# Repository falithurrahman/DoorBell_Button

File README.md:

### Description
In this repository, i made a doorbell using ESP8266-01 as a controller. This doorbell will play local mp3 file as notification sound through 3.5mm audio jack in my laptop, since i install home assistant server on docker in Ubuntu laptop. The audio jack in my laptop is connected to external speaker that will boost notification sound volume. I will cover up the details of this project in 2 parts. First is setting up doorbell hardware. Second is configuring home assistant server.

### First part, Doorbell Hardware

#### Tools and Equipments
Here is the parts we need to make physical doorbell button.
* ESP8266-01 Module
* Push Button
* BD140 Transistor
* 2x 18650 Li-Ion Battery
* 2x 5mm LED Indicator

#### Wiring Diagram
This section will cover wiring diagram from doorbell button. The detailed schematic and board file can be downloaded in the controller board folder. <br>

I used 2x 18650 Li-Ion battery to power this circuit. Those batteries will have parallel connection to increase the capacity (mAh). Higher capacity will make this battery more durable. I have tried this configuration, and the battery i use can last 4-5 days. So i have to replace the battery once every 4-5 days for charging.

#### Code
I use ESPHome firmware running on ESP8266-01 device. Since i use ESPHome, the code will be in yaml file. You can download the code inside Code folder with ESP01_BellControl.yaml filename. Pushbutton and indicator LED are attached to GPI02 and GPIO0 respectively. Button debounce filter is added to binary sensor in order to minimize misreading which is caused by debounce.
````yaml
switch:
  - platform: gpio
    id: indikator
    inverted: true
    name: LED Indikator
    pin: GPIO0

binary_sensor:
  - platform: gpio
    id: button
    name: Doorbell Button
    pin:
      number: GPIO2
      mode: INPUT_PULLUP
      inverted: true
    filters:
      - delayed_on: 25ms
      - delayed_off: 25ms
````

### Second Part, Home Assistant Configuration

#### Software Requirement
I am intended to make customized mp3 file played as notification sound through 3.5mm audio jack. This file is stored in local hard drive inside home assistant server. An add-ons is need to be installed to fulfill this purpose. To install the add-ons, follow these steps.
* In your home assisstant, go to supervisor -> Add-ons Store.
* Under repositories part, where we configure which add-on repositories to fetch data from, copy-paste this link. Then click 'Add'. It might take a bit, be patient. <br>
https://github.com/bestlibre/hassio-addons
* When the add-ons successfully installed, start the service.
* Add these line to your configuration.yaml file 
````yaml
# Mopidy addon for hass.io
media_player:
  platform: mpd
  host: YOUR.HOST.IP
````
* Restart home assistant server. Now we have Mopidy add-ons running in home assistant server.

After installing the add-ons, we need to configure it. As we can see at mopidy add-ons page, there are several variables that we can configure. Since our purpose is to play local mp3 file as notification sound, we need to enable local file scan and set the directory where the mp3 is stored. It can be done by writing these line
````yaml
local_scan: true
options:
  - name: local/media_dir
    value: /share/mopidy/media
````
In the example above, i place my mp3 file inside /share/mopidy/media. Then, restart home assistant server.

Next step, we will play the audio file stored in local drive through home assistant. To play the audio, follow the steps below.
* Go to Mopidy add-ons store page, and open web user interface. 
* We will see there are three options: image, iris, moped.Click on iris.
   
* At iris homepage, go to browse -> local media -> tracks
  <p align="center">
   <br>
   <br>
   <br>
  </p>
Or in short, you can access the link below <br>
http://"home_assistant_server_IP":6680/iris/library/browse/local%3Adirectory%3Ftype%3Dtrack <br>
Replace home_assistant_server_IP with the IP of home assistant without "" mark. <br>
* Find audio file we need, click on the three dots (...) and click on "Copy URI". Now we have the internal ID of this file in our clipboard. <br>
  <p align="center">
   <br>
   <br>
  </p>
* Go to developer tools -> service tab. Choose 'media_player.play_media' for service and 'media_player.mpd' for entity. For service data, fill it with line below
    ````yaml
    {
    "entity_id": "media_player.mpd",
    "media_content_type": "music",
    "media_content_id": "..."
    }
    ````
    Replace the media_content_id value with the URI file we copy. <br>
    <p align="center">
     <br>
    </p>
* Click "Call Service". The file should now be played via the 3.5mm headphone jack. Now we can use it in any automation.

#### Adding Automation
Now we reached the step when we finished configuring both hardware and software. The last step is to combine both of them by creating automation. I attach my automation.yaml file inside code folder. There are several things that i'd like to highlight. First is volume setting for our mp3 audio notification. We can adjust the volume by calling service called `media_player.volume_set`. The volume that we can set ranged from 0 to 1. I use 0.5 in my automation.
````yaml
  action:
  - data:
      entity_id: media_player.mpd
      volume_level: 0.5
    entity_id: media_player.mpd
    service: media_player.volume_set
````
Second is notification feature within home assistant apps. If we installed home assistant in our android or iOS phone, we can send a push notification everytime the automation happens. We do it by call service named `notify`. If we have more than one device and we want to send the notification at once, we have to modify `configuration.yaml` file. We add this line. `service:` is the name of our device. We can add more than one device.
````yaml
notify:
  - name: ALL_DEVICES
    platform: group
    services:
      - service: mobile_app_mi_9
      - service: mobile_app_asus_z010d
      - service: mobile_app_asus_z00ed
      - service: mobile_app_asus_t00f
````
Within the `automation.yaml` file, we call `notify.all_devices` service since the group name of our device is `ALL_DEVICES` in the `configuration.yaml file`.
````yaml
  action:
  - data:
      message: Ada Tamu!
    service: notify.all_devices
````

#### References
* TTS using built in RPi3 analogue audio output with Hassio <br>
https://community.home-assistant.io/t/tts-using-built-in-rpi3-analogue-audio-output-with-hassio/32475
*

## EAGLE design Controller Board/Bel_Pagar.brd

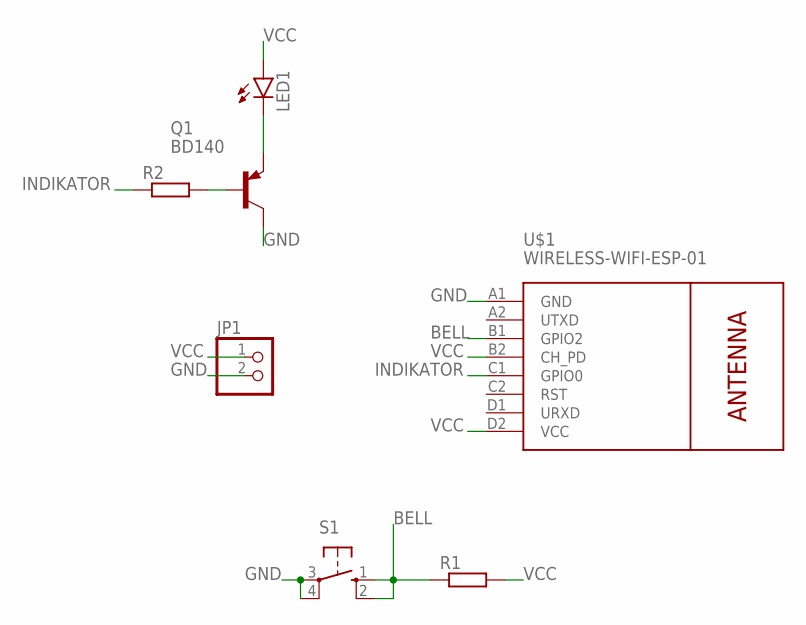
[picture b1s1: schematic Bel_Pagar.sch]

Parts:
JP1: PINHD-1X2; 1X02
LED1: LED5MM
Q1: BD140; TO126
R1, R2: R-EU_0207/10; 0207/10
S1: 10-XX; B3F-10XX
U$1: WIRELESS-WIFI-ESP-01

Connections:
BELL: R1.1, S1.1 (S), S1.2 (S1), U$1.B1 (GPIO2)
GND: JP1.2, Q1.2 (C), S1.3, S1.4 (P1), U$1.A1 (GND)
INDIKATOR: R2.1, U$1.C1 (GPIO0)
unnamed: Q1.3 (B), R2.2
unnamed: LED1.K (C), Q1.1 (E)
VCC: JP1.1, LED1.A, R1.2, U$1.B2 (CH_PD), U$1.D2 (VCC)

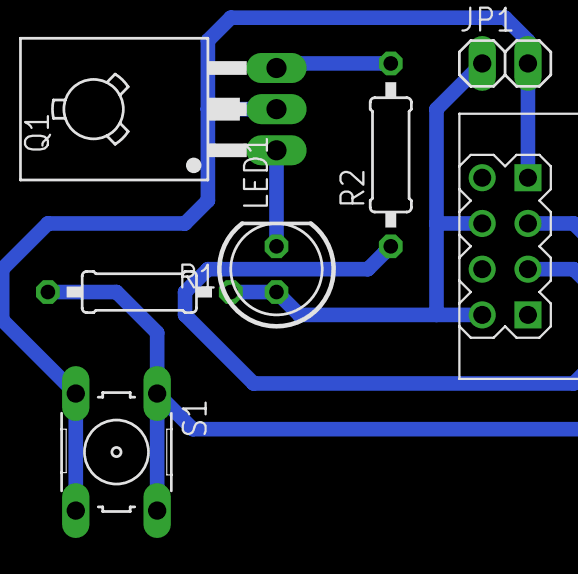
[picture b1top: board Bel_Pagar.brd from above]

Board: 2 copper layers, 7 parts (0 on the bottom side), 6 nets.

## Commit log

2020-04-19 Add controller board file
2020-05-02 Add description in readme file
2020-05-02 Remove 7805 from controller board
2020-05-02 Add schematic picture
2020-05-02 Add tools equipments and wiring diagram in readme file
2020-05-02 Add ESP8266 controller yaml code
2020-05-02 Add details on esp8266 controller yaml code
2020-05-02 Add picture to ease mopidy configuration
2020-05-02 Add software requirement on home assistant configuration
2020-05-02 Edit software requirement on home assistant configuration
2020-05-03 Edit pictures alignment in readme file
2020-05-03 Add automation code for doorbell
2020-05-03 Add automation section in readme file
2020-05-03 Add reference section in readme file

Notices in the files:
parts and their libraries:
diy-modules: Released under the Creative Commons Attribution 4.0 International License: http://creativecommons.org/licenses/by/4.0
